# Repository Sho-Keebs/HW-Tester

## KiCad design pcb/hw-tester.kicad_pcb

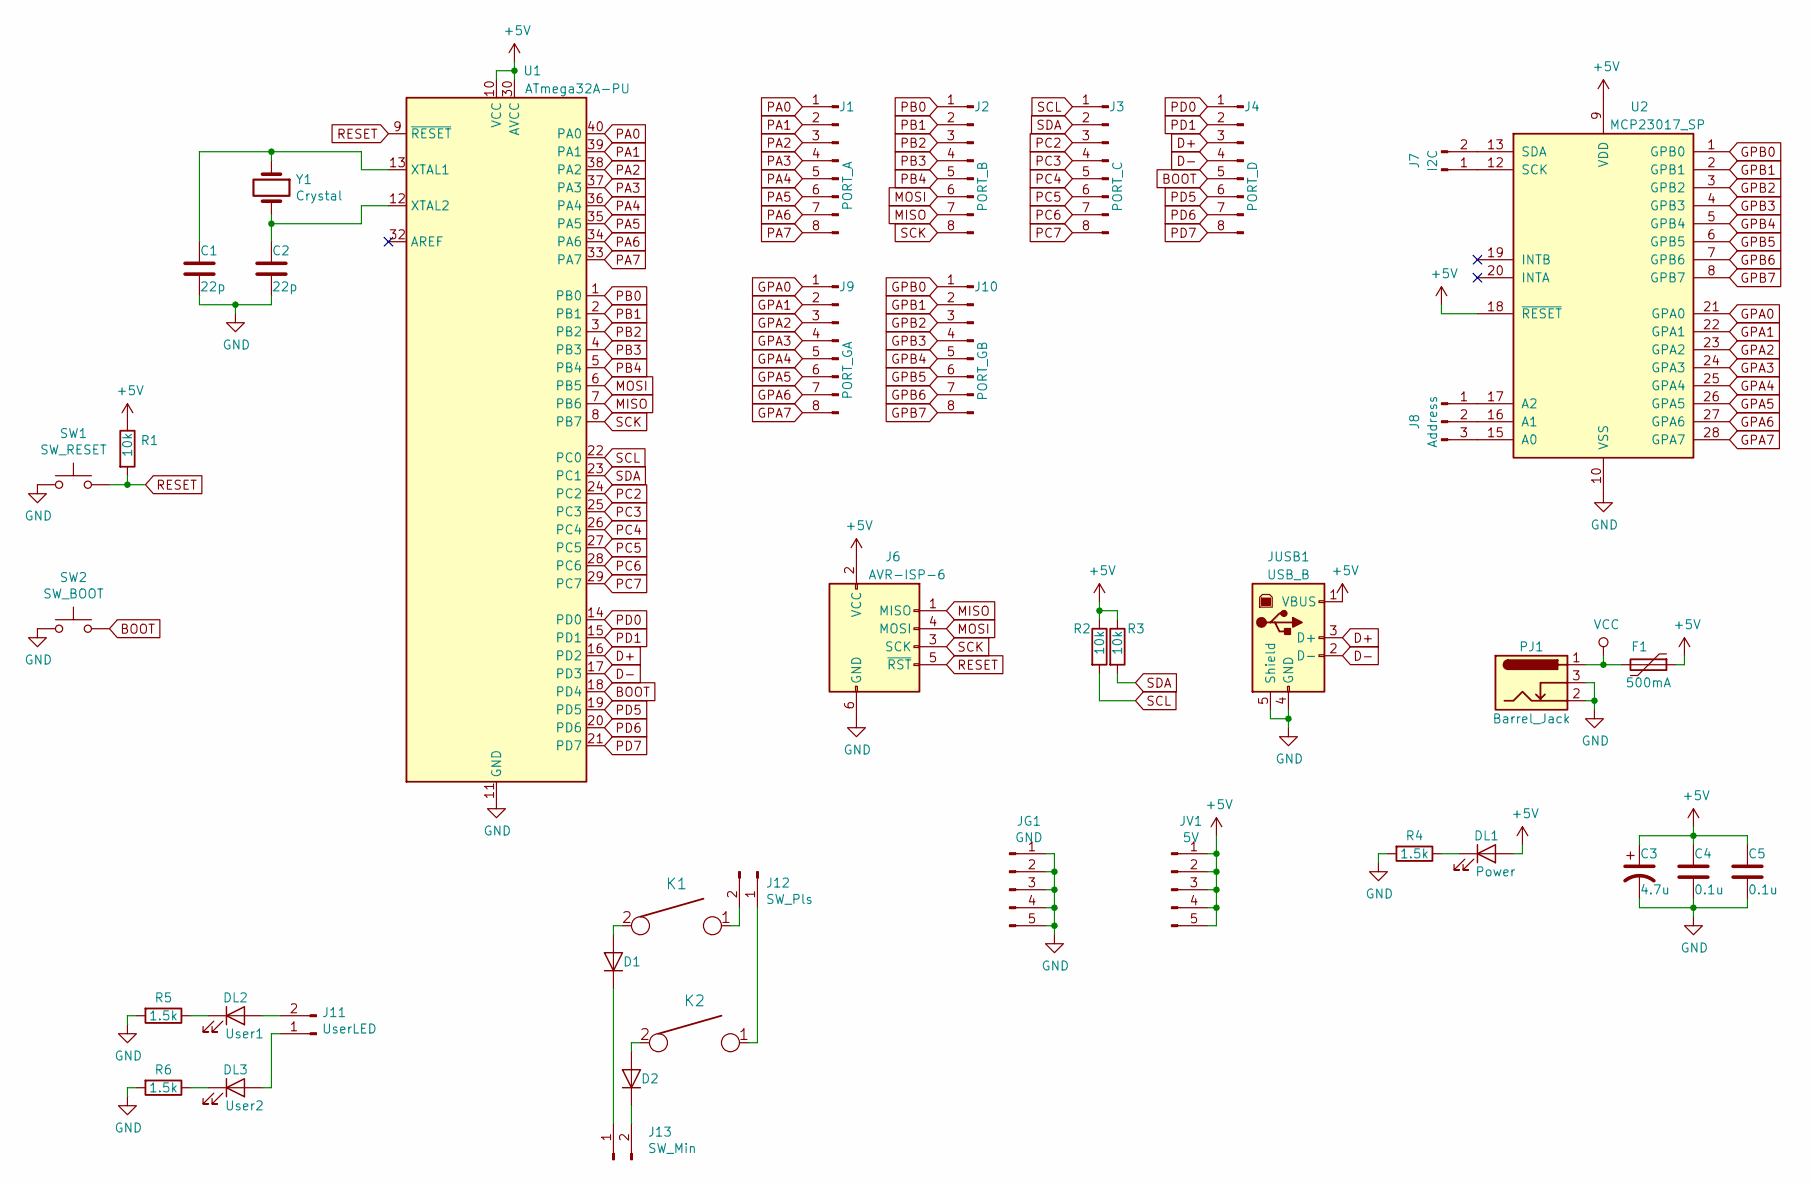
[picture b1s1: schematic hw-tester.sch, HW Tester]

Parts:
C1, C2: 22p; C_Disc_D3.8mm_W2.6mm_P2.50mm
C3: 4.7u; CP_Radial_D4.0mm_P1.50mm
C4, C5: 0.1u; C_Disc_D3.8mm_W2.6mm_P2.50mm
D1, D2: D; D_DO-35_SOD27_P7.62mm_Horizontal
DL1: Power; LED_D3.0mm
DL2: User1; LED_D3.0mm
DL3: User2; LED_D3.0mm
F1: 500mA; C_Disc_D9.0mm_W5.0mm_P10.00mm
J1: PORT_A; PinHeader_1x08_P2.54mm_Vertical
J2: PORT_B; PinHeader_1x08_P2.54mm_Vertical
J3: PORT_C; PinHeader_1x08_P2.54mm_Vertical
J4: PORT_D; PinHeader_1x08_P2.54mm_Vertical
J6: AVR-ISP-6; PinHeader_2x03_P2.54mm_Vertical
J7: I2C; PinHeader_1x02_P2.54mm_Vertical
J8: Address; PinHeader_1x03_P2.54mm_Vertical
J9: PORT_GA; PinHeader_1x08_P2.54mm_Vertical
J10: PORT_GB; PinHeader_1x08_P2.54mm_Vertical
J11: UserLED; PinHeader_1x02_P2.54mm_Vertical
J12: SW_Pls; PinHeader_1x02_P2.54mm_Vertical
J13: SW_Min; PinHeader_1x02_P2.54mm_Vertical
JG1: GND; PinHeader_1x05_P2.54mm_Vertical
JUSB1: USB_B; USB_B_OST_USB-B1HSxx_Horizontal
JV1: 5V; PinHeader_1x05_P2.54mm_Vertical
K1, K2: KEYSW; Mx_Alps_100
PJ1: Barrel_Jack; BarrelJack_Horizontal
R1, R2, R3: 10k; R_Axial_DIN0207_L6.3mm_D2.5mm_P7.62mm_Horizontal
R4, R5, R6: 1.5k; R_Axial_DIN0207_L6.3mm_D2.5mm_P7.62mm_Horizontal
SW1: SW_RESET; SW_PUSH_6mm
SW2: SW_BOOT; SW_PUSH_6mm
U1: ATmega32A-PU; DIP-40_W15.24mm_Socket
U2: MCP23017_SP; DIP-28_W7.62mm_Socket
Y1: Crystal; Crystal_HC49-U_Vertical

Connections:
+5V: C3.1, C4.1, C5.1, DL1.2 (A), F1.1, J6.2 (VCC), JUSB1.1 (VBUS), JV1.1, JV1.2, JV1.3, JV1.4, JV1.5, R1.1, R2.1, R3.1, U1.10 (VCC), U1.30 (AVCC), U2.9 (VDD), U2.18 (~RESET~)
BOOT: J4.5, SW2.2, U1.18 (PD4)
D+: J4.3, JUSB1.3 (D+), U1.16 (PD2)
D-: J4.4, JUSB1.2 (D-), U1.17 (PD3)
GND: C1.2, C2.2, C3.2, C4.2, C5.2, J6.6 (GND), JG1.1, JG1.2, JG1.3, JG1.4, JG1.5, JUSB1.4 (GND), JUSB1.5 (Shield), PJ1.2, PJ1.3, R4.2, R5.2, R6.2, SW1.1, SW2.1, U1.11 (GND), U1.31 (GND), U2.10 (VSS)
GPA0: J9.1, U2.21 (GPA0)
GPA1: J9.2, U2.22 (GPA1)
GPA2: J9.3, U2.23 (GPA2)
GPA3: J9.4, U2.24 (GPA3)
GPA4: J9.5, U2.25 (GPA4)
GPA5: J9.6, U2.26 (GPA5)
GPA6: J9.7, U2.27 (GPA6)
GPA7: J9.8, U2.28 (GPA7)
GPB0: J10.1, U2.1 (GPB0)
GPB1: J10.2, U2.2 (GPB1)
GPB2: J10.3, U2.3 (GPB2)
GPB3: J10.4, U2.4 (GPB3)
GPB4: J10.5, U2.5 (GPB4)
GPB5: J10.6, U2.6 (GPB5)
GPB6: J10.7, U2.7 (GPB6)
GPB7: J10.8, U2.8 (GPB7)
MISO: J2.7, J6.1 (MISO), U1.7 (PB6)
MOSI: J2.6, J6.4 (MOSI), U1.6 (PB5)
unnamed: C1.1, U1.13 (XTAL1), Y1.1
unnamed: C2.1, U1.12 (XTAL2), Y1.2
unnamed: D1.1 (K), J13.1
unnamed: D1.2 (A), K1.2
unnamed: D2.1 (K), J13.2
unnamed: D2.2 (A), K2.2
unnamed: DL1.1 (K), R4.1
unnamed: DL2.1 (K), R5.1
unnamed: DL2.2 (A), J11.2
unnamed: DL3.1 (K), R6.1
unnamed: DL3.2 (A), J11.1
unnamed: J7.1, U2.12 (SCK)
unnamed: J7.2, U2.13 (SDA)
unnamed: J8.1, U2.17 (A2)
unnamed: J8.2, U2.16 (A1)
unnamed: J8.3, U2.15 (A0)
unnamed: J12.1, K2.1
unnamed: J12.2, K1.1
PA0: J1.1, U1.40 (PA0)
PA1: J1.2, U1.39 (PA1)
PA2: J1.3, U1.38 (PA2)
PA3: J1.4, U1.37 (PA3)
PA4: J1.5, U1.36 (PA4)
PA5: J1.6, U1.35 (PA5)
PA6: J1.7, U1.34 (PA6)
PA7: J1.8, U1.33 (PA7)
PB0: J2.1, U1.1 (PB0)
PB1: J2.2, U1.2 (PB1)
PB2: J2.3, U1.3 (PB2)
PB3: J2.4, U1.4 (PB3)
PB4: J2.5, U1.5 (PB4)
PC2: J3.3, U1.24 (PC2)
PC3: J3.4, U1.25 (PC3)
PC4: J3.5, U1.26 (PC4)
PC5: J3.6, U1.27 (PC5)
PC6: J3.7, U1.28 (PC6)
PC7: J3.8, U1.29 (PC7)
PD0: J4.1, U1.14 (PD0)
PD1: J4.2, U1.15 (PD1)
PD5: J4.6, U1.19 (PD5)
PD6: J4.7, U1.20 (PD6)
PD7: J4.8, U1.21 (PD7)
RESET: J6.5 (~RST), R1.2, SW1.2, U1.9 (~RESET)
SCK: J2.8, J6.3 (SCK), U1.8 (PB7)
SCL: J3.1, R2.2, U1.22 (PC0)
SDA: J3.2, R3.2, U1.23 (PC1)
VCC: F1.2, PJ1.1

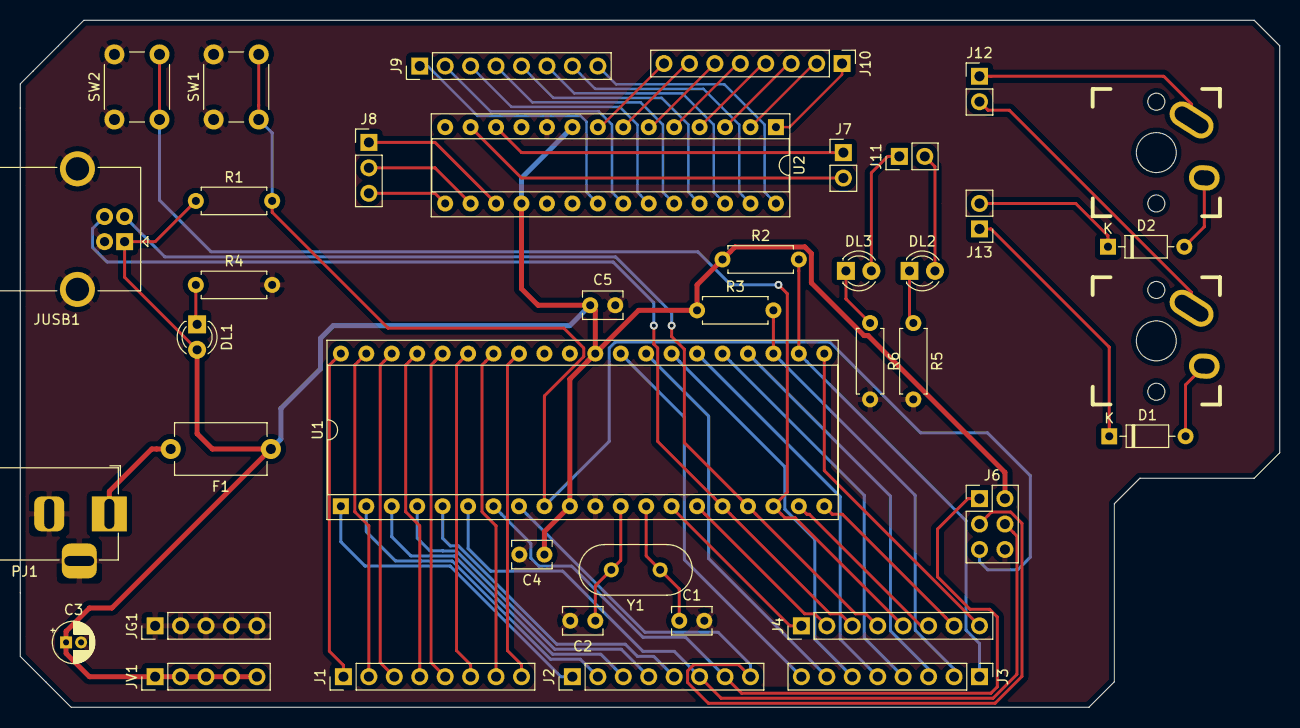
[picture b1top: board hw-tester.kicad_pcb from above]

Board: 2 copper layers, 125.7 x 68.6 mm, 40 parts (0 on the bottom side), 70 nets.

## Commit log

2020-01-27 Release v0.1
